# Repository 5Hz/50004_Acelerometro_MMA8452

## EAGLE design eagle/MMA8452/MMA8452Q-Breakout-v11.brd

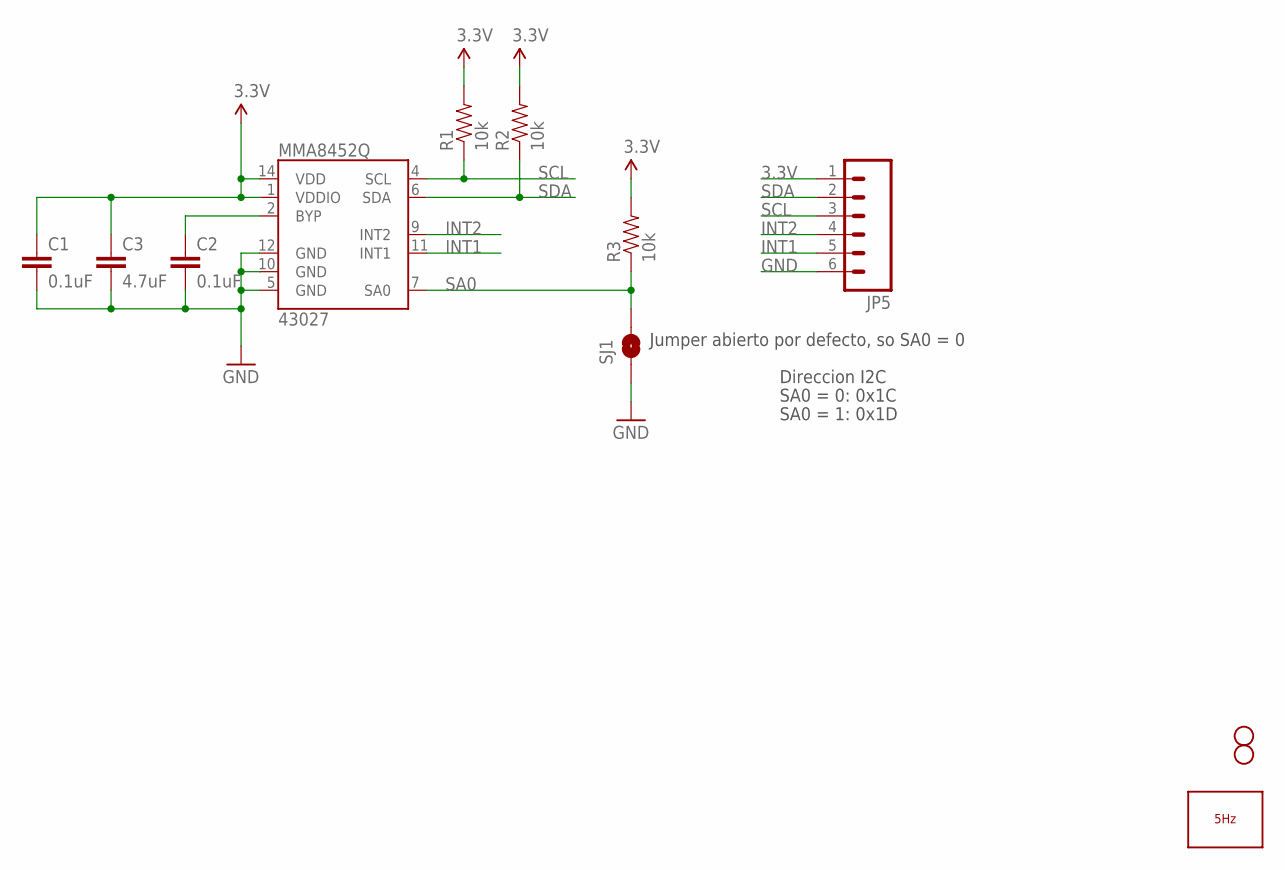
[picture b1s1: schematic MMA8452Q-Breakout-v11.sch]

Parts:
C1, C2: 0.1uF; 0402-CAP
C3: 4.7uF; 0402-CAP
JP3, JP4: STAND-OFF
JP5: M06SIP; 1X06
LOGO1: LOGO_5HZ_MAIN_5MM; 5HZ_LOGO_MAIN_5MM
MMA8452Q: 43027; QFN-16_0.5MM
R1, R2, R3: 10k; 0402-RES
SJ1: SOLDERJUMPERNO; SJ_2S-NO

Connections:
3.3V: C1.1, C3.1, JP5.1, MMA8452Q.1 (VDDIO), MMA8452Q.14 (VDD), R1.2, R2.2, R3.2
BYP: C2.1, MMA8452Q.2 (BYP)
GND: C1.2, C2.2, C3.2, JP5.6, MMA8452Q.5 (GND), MMA8452Q.10 (GND), MMA8452Q.12 (GND), SJ1.1
INT1: JP5.5, MMA8452Q.11 (INT1)
INT2: JP5.4, MMA8452Q.9 (INT2)
SA0: MMA8452Q.7 (SA0), R3.1, SJ1.2
SCL: JP5.3, MMA8452Q.4 (SCL), R1.1
SDA: JP5.2, MMA8452Q.6 (SDA), R2.1

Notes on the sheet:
Direccion I2C
SA0 = 0: 0x1C
SA0 = 1: 0x1D
Jumper abierto por defecto, so SA0 = 0

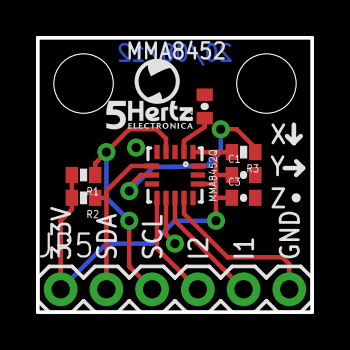
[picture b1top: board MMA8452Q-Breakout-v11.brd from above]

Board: 2 copper layers, 15.2 x 15.2 mm, 12 parts (1 on the bottom side), 8 nets.

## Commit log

2014-01-09 creación
